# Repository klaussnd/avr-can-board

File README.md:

# Generic AVR CAN board

This project is a generic [AVR](https://en.wikipedia.org/wiki/AVR_microcontrollers) board with [CAN](https://en.wikipedia.org/wiki/CAN_bus) onboard.
It is designed to be a small-size (55mm x 30mm) versatile board for CAN applications.

The main microcontroller is an ATmega168P or similar (any TQFP32 ATmega can be soldered on the board), for CAN the MCP2515 controller and MCP2551 transceiver are used.
All free pins are routed to the side pin rows (2.54mm spacing), similar to the popular Arduinos.
A voltage regulator (LP2950) is included to use a wide range of voltage sources, typically 12V or 24V supply voltage goes along with the CAN bus so you can spare an additional power supply.
Basic components are SMD 0805 size, use zero ohm 0805 resistors as bridges.

To save cost and PCB space, there is no onboard programmer; an external programmer must be plugged to flash the MCU.
The board has a connector to program (P1) which fits the [mysmartUSB MK2](https://shop.myavr.com/systemboards%20and%20programmer/mySmartUSB%20MK2%20(Programmer%20und%20Bridge).htm?sp=article.sp.php&artID=200179) but any programmer can be wired.

## Configurable features

The board can be configured in separate ways by soldering or not certain bridges or resistors.

* CAN connector can be either two RJ11 or a Molex SPOX
* MCU clock source:
    - internal clock
    - separate crystal (solder crystal and C2 and C3)
    - clock from the MCP2515 (solder a bridge to JP1 and program the MCP2515 accordingly)
* Possibility of using power-safe mode of the MCP2551: solder JP2 _instead of_ R4 (and program the MCP2515 accordingly)
* Select the edge steepness of the CAN signal by adjusting the value of R4 or JP2 (see [MCP2551 datasheet](https://ww1.microchip.com/downloads/en/DeviceDoc/20001667G.pdf))
* I2C pullup resistors: Solder R2 and R3
* Analogue input circuit if required (L1, C8, C9)

## Cape

A template for a cape (PCB which can be plugged onto the controller board as an extension) is included. Add your own circuit to the cape template.

## Firmware

A few tips:

* The SS pin (B2) of the ATmega _must_ be configured as an output, otherwise the SPI communication with the MCP2515 doesn't work.
* As library for the CAN controller you can use, for example, [avr-canlib](https://github.com/klaussnd/avr-can-lib) or [modm](https://modm.io/).

## License

The circuits are licensed under the terms of the [GNU Affero General Public License](https://www.gnu.org/licenses/agpl-3.0.en.html).

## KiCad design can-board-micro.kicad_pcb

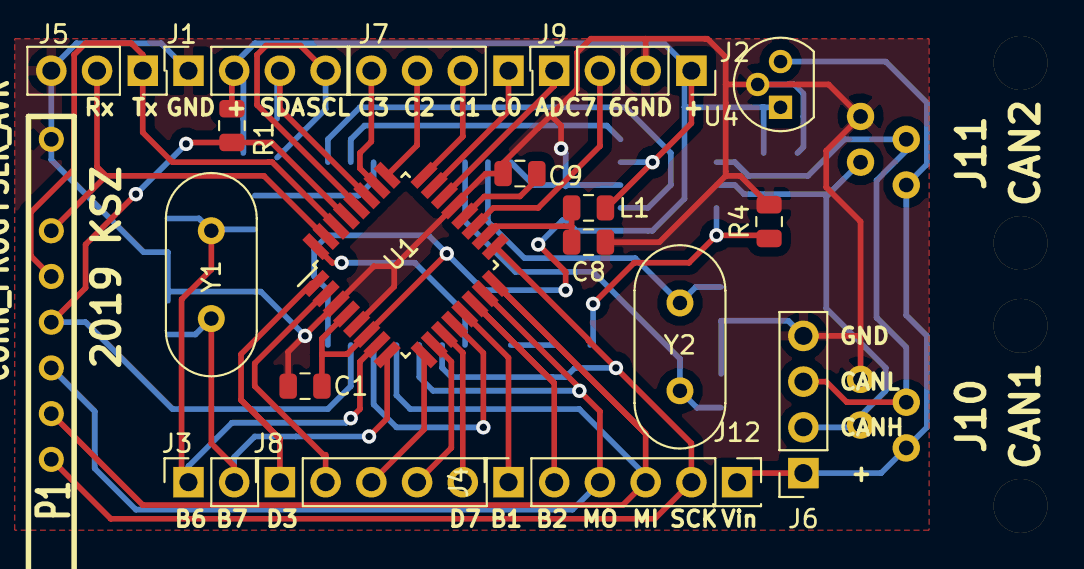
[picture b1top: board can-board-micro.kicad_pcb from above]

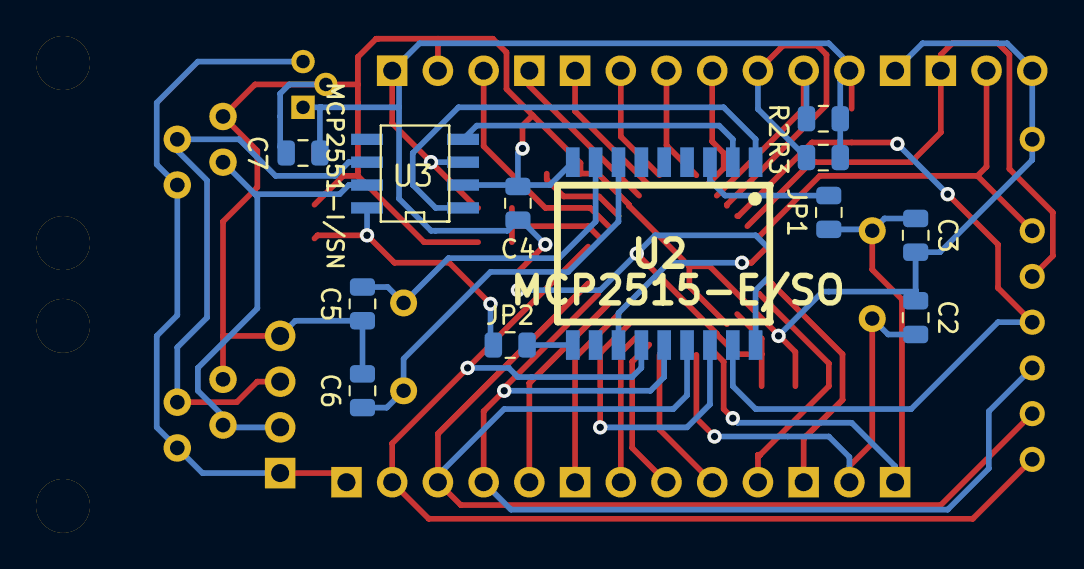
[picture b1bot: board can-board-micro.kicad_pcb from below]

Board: 2 copper layers, 35 parts (12 on the bottom side), 39 nets.

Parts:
C1, C4, C8, C9: 100n; C_0805_2012Metric
C2, C3: 22p; C_0805_2012Metric
C5, C6: 33p; C_0805_2012Metric
C7: 4.7u; C_0805_2012Metric
J1: I2C; PinSocket_1x04_P2.54mm_Vertical
J2: Vcc; PinSocket_1x02_P2.54mm_Vertical
J3: PORTB_2; PinSocket_1x02_P2.54mm_Vertical
J4: PORTB_1; PinSocket_1x05_P2.54mm_Vertical
J5: USART; PinSocket_1x03_P2.54mm_Vertical
J6: CAN; PinSocket_1x04_P2.54mm_Vertical
J7: PORTC; PinSocket_1x04_P2.54mm_Vertical
J8: PORTD; PinSocket_1x05_P2.54mm_Vertical
J9: ADC; PinSocket_1x02_P2.54mm_Vertical
J10: CAN1; RJ11_RO
J11: CAN2; RJ11_RO
J12: 12V; PinSocket_1x01_P2.54mm_Vertical
JP1: clk; R_0805_2012Metric
JP2: SLEEP; R_0805_2012Metric
L1: 10u; L_0805_2012Metric
P1: CONN_PROG+SER_AVR; SIL-10_MYAVR+SER
R1, R4: 10k; R_0805_2012Metric
R2, R3: 4.7k; R_0805_2012Metric
U1: ATMEGA168PA-AU; TQFP-32_7x7mm_P0.8mm
U2: MCP2515-E/SO; SOIC18_300
U3: MCP2551-I/SN; SOIC8_150
U4: LP2950-5.0_TO92; TO-92
Y1: 7.3728MHz; Crystal_HC49-U_Vertical
Y2: 16MHz; Crystal_HC49-U_Vertical

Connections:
/SCL: J1.4, R3.2, U1.28
/SDA: J1.3, R2.2, U1.27
GNDD: C1.2, C2.2, C3.2, C4.2, C5.2, C6.2, C7.2, C8.2, C9.2, J1.1, J2.2, J5.3, J6.4, J10.5, J11.5, P1.10, R4.2, U1.3, U1.5, U1.21, U2.9, U3.2, U4.2
unnamed: C2.1, J3.2, U1.8, Y1.2
unnamed: C3.1, J3.1, JP1.1, U1.7, Y1.1
unnamed: C5.1, U2.8, Y2.2
unnamed: C6.1, U2.7, Y2.1
unnamed: C8.1, L1.2, U1.18
unnamed: C9.1, U1.20
unnamed: J4.1, U1.13
unnamed: J4.2, U1.14
unnamed: J4.3, P1.5, U1.15, U2.14
unnamed: J4.4, P1.4, U1.16, U2.15
unnamed: J4.5, P1.3, U1.17, U2.13
unnamed: J5.1, P1.7, U1.30
unnamed: J5.2, P1.8, U1.31
unnamed: J7.1, U1.23
unnamed: J7.2, U1.24
unnamed: J7.3, U1.25
unnamed: J7.4, U1.26
unnamed: J8.1, U1.1
unnamed: J8.2, U1.2
unnamed: J8.3, U1.9
unnamed: J8.4, U1.10
unnamed: J8.5, U1.11
unnamed: J9.1, U1.22
unnamed: J9.2, U1.19
unnamed: J6.1, J10.2, J11.2, J12.1, U4.3
unnamed: J6.2, J10.3, J11.3, U3.7
unnamed: J6.3, J10.4, J11.4, U3.6
unnamed: JP1.2, U2.3
unnamed: JP2.1, R4.1, U3.8
unnamed: JP2.2, U2.10
unnamed: P1.6, R1.2, U1.29, U2.17
unnamed: U1.12, U2.16
unnamed: U1.32, U2.12
unnamed: U2.1, U3.1
unnamed: U2.2, U3.4
VCC: C1.1, C4.1, C7.1, J1.2, J2.1, L1.1, R1.1, R2.1, R3.1, U1.4, U1.6, U2.18, U3.3, U4.1

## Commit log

2021-12-26 Add micro CAN adapter
2021-12-26 Add empty cape for micro CAN board
2021-12-27 Add documentation
